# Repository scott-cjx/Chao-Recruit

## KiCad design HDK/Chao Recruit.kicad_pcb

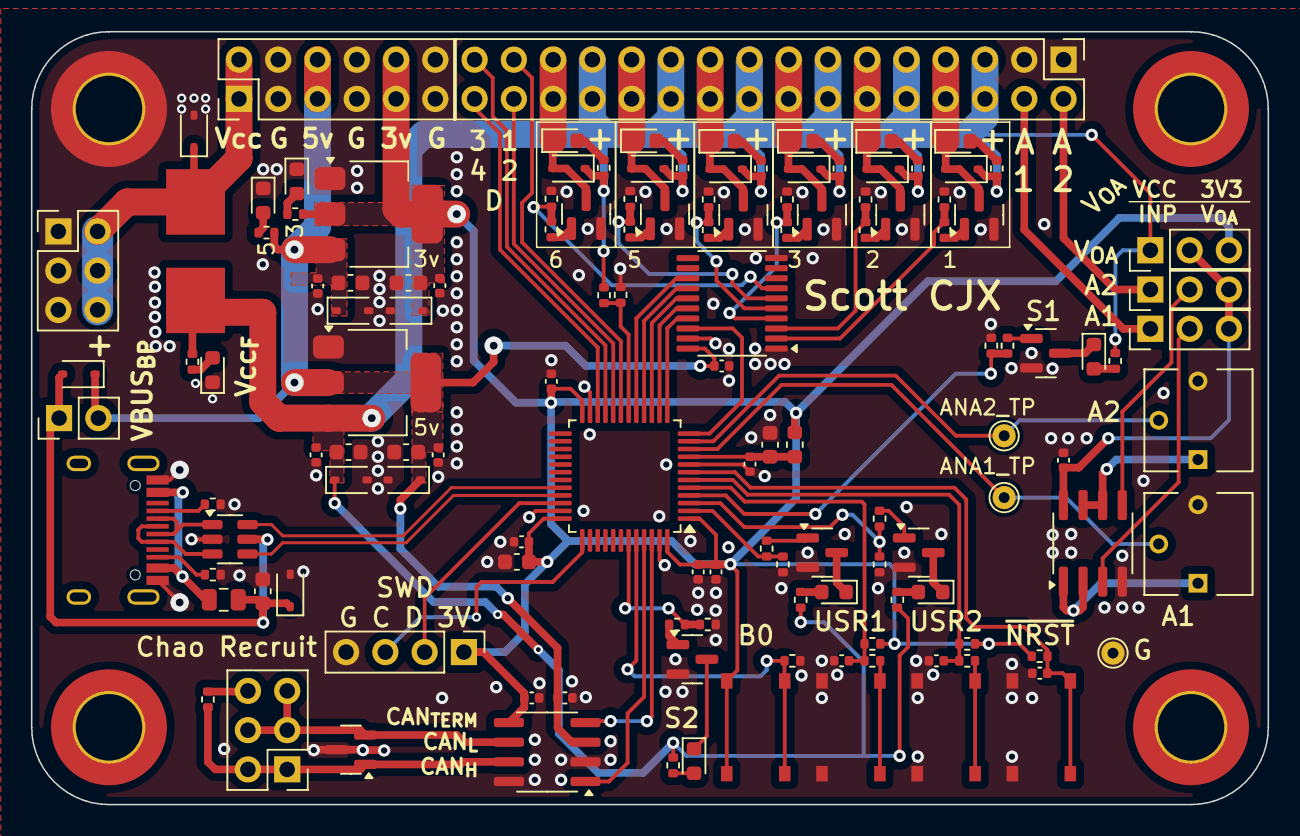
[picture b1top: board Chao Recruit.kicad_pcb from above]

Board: 2 copper layers, 80.0 x 50.0 mm, 137 parts (0 on the bottom side), 90 nets.

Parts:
C101, C102, C103, C104, C107, C108, C109, C112, C113, C116, C201, C202, C203, C204, C501, C502: 100n; C_0402_1005Metric
C105, C106, C110, C111, C114, C115, C301: 10u; C_0603_1608Metric
D101, D202, D205, D209, D212, D214, D216: D; D_SOD-323
D103: Red LED; LED_0603_1608Metric
D106, D109, D206: CESD12VD3; D_SOD-323
D107: CESD3V3D3ZA; D_SOD-323
D108, D111: Red; LED_0603_1608Metric
D110, D301: CESD5V0D3ZA; D_SOD-323
D201, D204, D208, D211, D213: Yellow; LED_0603_1608Metric
D203, D207, D210, D215, D217: Yellow LED; LED_0603_1608Metric
D501: ESDCAN24-2BLY; SOT-23
F101: Fuse; FUSE-Littelfuse_Nano2_154x
F301: SMD0805-050-16V; Fuse_0805_2012Metric
H101, H102, H103, H104: MountingHole_Pad; MountingHole_4.3mm_M4_DIN965_Pad_TopBottom
J101: SWD; PinHeader_1x04_P2.54mm_Vertical
J202: Pwr Interconnect; PinHeader_2x06_P2.54mm_Vertical
J204: Sig Interconnect; PinHeader_2x16_P2.54mm_Vertical
J205: Pwr; PinHeader_2x03_P2.54mm_Vertical
J207: CanBus; PinHeader_2x03_P2.54mm_Vertical
J211, J213, J214: Conn_01x03; PinHeader_1x03_P2.54mm_Vertical
J301: USB_C; USBC_HRO_TYPE-C-31-M-12
JP101: Jumper_2_Open; PinHeader_1x02_P2.54mm_Vertical
L101: CBG160808U121T; L_0603_1608Metric
Q201, Q202, Q203, Q204, Q205, Q206, Q207, Q208, Q209, Q210: AO3400A; SOT-23
R101, R104, R105, R228, R229: 10k; R_0402_1005Metric
R102, R106, R107, R201, R204, R207, R210, R213, R216, R219, R222, R226, R233: 4k7; R_0402_1005Metric
R103, R230, R232: 1k; R_0402_1005Metric
R202, R203, R208, R209, R214, R215, R220, R221, R225, R231: 100k; R_0402_1005Metric
R205, R206, R211, R212, R217, R218, R223, R224, R227, R234: 10; R_0402_1005Metric
R301, R302: 5k1; R_0402_1005Metric
R501: 120; R_0402_1005Metric
RV201, RV202: RV 10k; RV_Bourns_3362
SW101, SW102, SW201, SW202: SW_Push; PushBtn_TS-1187A-B-A-B
TP201: ANA1_TP; TestPoint_THTPad_D1.5mm_Drill0.7mm
TP202: GND_TP; TestPoint_THTPad_D1.5mm_Drill0.7mm
TP203: ANA2_TP; TestPoint_THTPad_D1.5mm_Drill0.7mm
U101: STM32F072C8T6; LQFP-48_7x7mm_P0.5mm
U102: AMS1117-3.3; SOT-223-3_TabPin2
U103: AMS1117-5.0; SOT-223-3_TabPin2
U201: OPA2197IDR; SOIC-8_3.9x4.9mm_P1.27mm
U202: SN74HC245PWR; TSSOP-20_4.4x6.5mm_P0.65mm
U301: USBLC6-2SC6; SOT-23-6
U501: TJA1042T-3; SOIC-8_3.9x4.9mm_P1.27mm

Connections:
+3V3: C101.1, C102.1, C103.1, C104.1, C105.1, C111.1, C112.1, C502.1, D107.1 (K), J101.1, J202.9, J202.10, J211.3, L101.1, R104.1, R106.1, R228.1, R229.1, SW101.2, U101.1 (VBAT), U101.24 (VDD), U101.36 (VDDIO2), U101.48 (VDD), U102.2 (VO), U501.5 (VIO)
+5V: C109.1, C110.1, C115.1, C116.1, C204.1, C501.1, D101.1 (K), D106.1 (K), D110.1 (K), J202.5, J202.6, JP101.2 (B), R107.1, U102.3 (VI), U103.2 (VO), U202.20 (VCC), U501.3 (VCC)
/ANA1_MCU-PA0: RV201.2, TP201.1, U101.10 (PA0)
/ANA2_MCU-PA1: RV202.2, TP203.1, U101.11 (PA1)
/BOOT0: R105.1, SW101.1, U101.44 (BOOT0)
/CAN_RX_MCU-PB9: U101.46 (PB9), U501.4 (RXD)
/CAN_TX_MCU-PB8: U101.45 (PB8), U501.1 (TXD)
/Communications/CAN_H: D501.1 (K), J207.1, J207.2, R501.1, U501.7 (CANH)
/Communications/CAN_H_{TERMINATED}: J207.6, R501.2
/Communications/CAN_L: D501.2 (K), J207.3, J207.4, J207.5, U501.6 (CANL)
/DIG_IN1: J204.29, U101.19 (PB1)
/DIG_IN2: J204.30, U101.20 (PB2)
/DIG_IN3: J204.31, U101.21 (PB10)
/DIG_IN4: J204.32, U101.22 (PB11)
/HMI/ANA1_INP: J204.4, J213.1
/HMI/ANA1_OA: J213.2, U201.3 (+)
/HMI/ANA2_INP: J204.2, J214.1
/HMI/ANA2_OA: J214.2, U201.5 (+)
/HMI/MOS1-: D202.2 (A), D203.1 (K), J204.7, J204.8, Q201.3 (D)
/HMI/MOS1_CTRL: R202.1, R205.1, U202.2 (A0)
/HMI/MOS2-: D205.2 (A), D207.1 (K), J204.11, J204.12, Q203.3 (D)
/HMI/MOS2_CTRL: R208.1, R211.1, U202.3 (A1)
/HMI/MOS3-: D209.2 (A), D210.1 (K), J204.15, J204.16, Q205.3 (D)
/HMI/MOS3_CTRL: R214.1, R217.1, U202.4 (A2)
/HMI/MOS4-: D212.2 (A), D213.1 (K), J204.19, J204.20, Q207.3 (D)
/HMI/MOS4_CTRL: R220.1, R223.1, U202.5 (A3)
/HMI/MOS5-: D214.2 (A), D215.1 (K), J204.23, J204.24, Q209.3 (D)
/HMI/MOS5_CTRL: R225.1, R227.1, U202.6 (A4)
/HMI/MOS6-: D216.2 (A), D217.1 (K), J204.27, J204.28, Q210.3 (D)
/HMI/MOS6_CTRL: R231.1, R234.1, U202.7 (A5)
/HMI/USB1/CC1: J301.A5 (CC1), R301.1
/HMI/USB1/CC2: J301.B5 (CC2), R302.1
/HMI/USB1/_USB_D+: J301.A6 (D+), J301.B6 (D+), U301.3 (I/O2)
/HMI/USB1/_USB_D-: J301.A7 (D-), J301.B7 (D-), U301.1 (I/O1)
/MOS1_CTRL_MCU-PA2: U101.12 (PA2), U202.18 (B0)
/MOS2_CTRL_MCU-PA3: U101.13 (PA3), U202.17 (B1)
/MOS3_CTRL_MCU-PA4: U101.14 (PA4), U202.16 (B2)
/MOS4_CTRL_MCU-PA5: U101.15 (PA5), U202.15 (B3)
/MOS5_CTRL_MCU-PA6: U101.16 (PA6), U202.14 (B4)
/MOS6_CTRL_MCU-PA7: U101.17 (PA7), U202.13 (B5)
/NRST: C108.1, R104.2, SW102.1, U101.7 (NRST)
/STATUS_LED1_MCU-PB7: R215.1, R218.1, U101.43 (PB7)
/STATUS_LED2_MCU-PC15: R221.1, R224.1, U101.4 (PC15)
/SWCLK-PA14: J101.3, U101.37 (PA14)
/SWDIO-PA13: J101.2, U101.34 (PA13)
/USB1_MCU_D+: U101.32 (PA11), U301.6 (I/O1)
/USB1_MCU_D-: U101.33 (PA12), U301.4 (I/O2)
/USR_BTN1_MCU-PF0: C201.1, R228.2, R230.1, U101.5 (PF0)
/USR_BTN2_MCU-PF1: C202.1, R229.2, R232.1, U101.6 (PF1)
/USR_LED1_MCU-PC13: R203.1, R206.1, U101.2 (PC13)
/USR_LED2_MCU-PC14: R209.1, R212.1, U101.3 (PC14)
/V_{SENSE}_MCU-PB0: R101.2, R103.1, U101.18 (PB0)
GND: C101.2, C102.2, C103.2, C104.2, C105.2, C106.2, C107.2, C108.2, C109.2, C110.2, C111.2, C112.2, C113.2, C114.2, C115.2, C116.2, C201.2, C202.2, C203.2, C204.2, C301.2, C501.2, C502.2, D103.1 (K), D106.2 (A), D107.2 (A), D108.1 (K), D109.2 (A), D110.2 (A), D111.1 (K), D206.2 (A), D301.2 (A), D501.3 (A), H101.1, J101.4, J202.3, J202.4, J202.7, J202.8, J202.11, J202.12, J204.1, J204.3, J205.1, J205.3, J205.5, J301.A1 (GND), J301.A12 (GND), J301.B1 (GND), J301.B12 (GND), Q201.2 (S), Q202.2 (S), Q203.2 (S), Q204.2 (S), Q205.2 (S), Q206.2 (S), Q207.2 (S), Q208.2 (S), Q209.2 (S), Q210.2 (S), R103.2, R105.2, R202.2, R203.2, R208.2, R209.2, R214.2, R215.2, R220.2, R221.2, R225.2, R231.2, R301.2, R302.2, RV201.3, RV202.3, SW102.2, SW201.2, SW202.2, TP202.1, U101.8 (VSSA), U101.23 (VSS), U101.35 (VSS), U101.47 (VSS), U102.1 (GND), U103.1 (GND), U201.4 (V-), U202.1 (A->B), U202.10 (GND), U202.19 (CE), U301.2 (GND), U501.2 (GND), U501.8 (STB)
unnamed: D103.2 (A), R102.2
unnamed: D108.2 (A), R106.2
unnamed: D111.2 (A), R107.2
unnamed: D201.2 (A), R201.2
unnamed: D201.1 (K), Q202.3 (D)
unnamed: D203.2 (A), R204.2
unnamed: D204.2 (A), R207.2
unnamed: D204.1 (K), Q204.3 (D)
unnamed: D207.2 (A), R210.2
unnamed: D208.2 (A), R213.2
unnamed: D208.1 (K), Q206.3 (D)
unnamed: D210.2 (A), R216.2
unnamed: D211.2 (A), R219.2
unnamed: D211.1 (K), Q208.3 (D)
unnamed: D213.2 (A), R222.2
unnamed: D215.2 (A), R226.2
unnamed: D217.2 (A), R233.2
unnamed: F301.1, J301.A4 (VBUS), J301.A9 (VBUS), J301.B4 (VBUS), J301.B9 (VBUS)
unnamed: Q201.1 (G), R205.2
unnamed: Q202.1 (G), R206.2
unnamed: Q203.1 (G), R211.2
unnamed: Q204.1 (G), R212.2
unnamed: Q205.1 (G), R217.2
unnamed: Q206.1 (G), R218.2
unnamed: Q207.1 (G), R223.2
unnamed: Q208.1 (G), R224.2
unnamed: Q209.1 (G), R227.2
unnamed: Q210.1 (G), R234.2
unnamed: R230.2, SW201.1
unnamed: R232.2, SW202.1
unnamed: RV201.1, U201.1, U201.2 (-)
unnamed: RV202.1, U201.6 (-), U201.7
VBUS_{USB1}: C301.1, D101.2 (A), D301.1 (K), F301.2, JP101.1 (A), U301.5 (VBUS)
VCC: D206.1 (K), F101.1, J202.1, J202.2, J205.2, J205.4, J205.6
VCC_{F}: C113.1, C114.1, D109.1 (K), D202.1 (K), D205.1 (K), D209.1 (K), D212.1 (K), D214.1 (K), D216.1 (K), F101.2, J204.5, J204.6, J204.9, J204.10, J204.13, J204.14, J204.17, J204.18, J204.21, J204.22, J204.25, J204.26, J211.1, R101.1, R102.1, R201.1, R204.1, R207.1, R210.1, R213.1, R216.1, R219.1, R222.1, R226.1, R233.1, U103.3 (VI)
VDDA: C106.1, C107.1, L101.2, U101.9 (VDDA)
V_{OA}: C203.1, J211.2, J213.3, J214.3, U201.8 (V+)

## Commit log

2025-01-06 try add download file
2025-01-06 try download button
2025-01-06 refactoring name
2025-01-06 fix download button
2025-01-06 fix page not found
2025-01-06 updated files
2025-01-06 updated documentation
2025-01-06 Deployed a10181b with MkDocs version: 1.6.1
2025-03-22 Deployed 53226c2 with MkDocs version: 1.6.1

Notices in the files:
HDK/Chao Recruit.kicad_pcb:
License: CERN-OHL-S-2.0
Copyright © Scott CJX
Licensed to Nanyang Venture Formula for NVF-2
